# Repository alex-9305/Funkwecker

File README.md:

# Funkwecker
Hardware- und Softwareentwicklung eines Funkweckers

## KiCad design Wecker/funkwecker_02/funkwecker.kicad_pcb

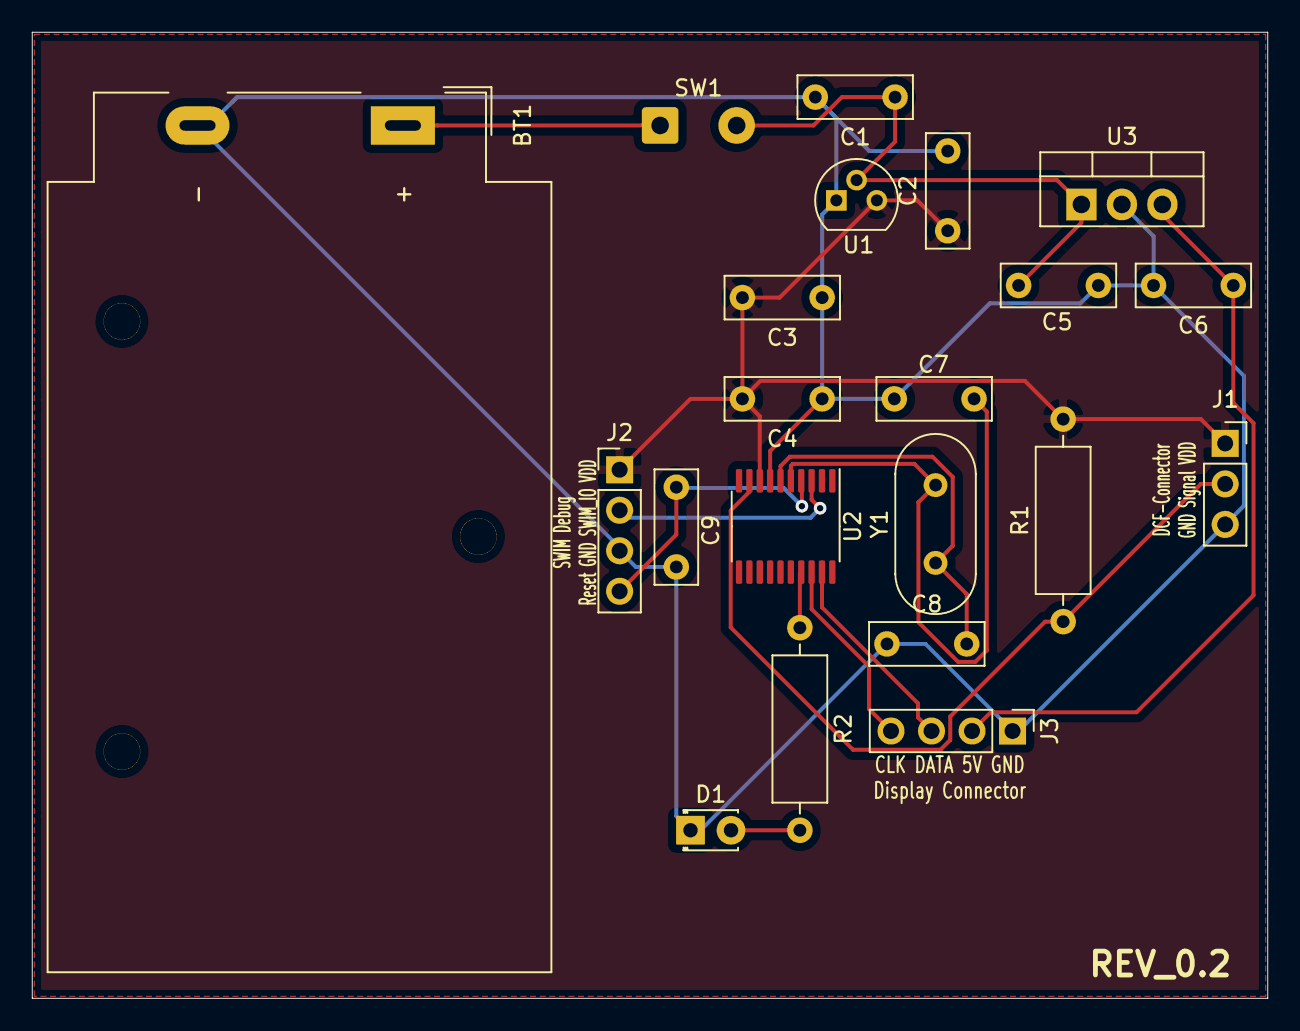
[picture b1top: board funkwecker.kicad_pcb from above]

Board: 2 copper layers, 77.5 x 60.6 mm, 21 parts (0 on the bottom side), 14 nets.

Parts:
BT1: 9VBlock; BatteryHolder_MPD_BA9VPC_1xPP3
C1, C2: 1µF; C_Disc_D7.0mm_W2.5mm_P5.00mm
C3, C9: 100nF; C_Disc_D7.0mm_W2.5mm_P5.00mm
C4: 10µF; C_Disc_D7.0mm_W2.5mm_P5.00mm
C5: 0.33µF; C_Disc_D7.0mm_W2.5mm_P5.00mm
C6: 0.1µF; C_Disc_D7.0mm_W2.5mm_P5.00mm
C7, C8: 20pF; C_Disc_D7.0mm_W2.5mm_P5.00mm
D1: Test_LED; LED_D1.8mm_W3.3mm_H2.4mm
J1: DCF77-Connector; PinSocket_1x03_P2.54mm_Vertical
J2: Debug-Interface; PinHeader_1x04_P2.54mm_Vertical
J3: LED-Display Connector (TM1637); PinHeader_1x04_P2.54mm_Vertical
R1: 100k; R_Axial_DIN0309_L9.0mm_D3.2mm_P12.70mm_Horizontal
R2: 1k; R_Axial_DIN0309_L9.0mm_D3.2mm_P12.70mm_Horizontal
SW1: Hauptschalter; SolderWire-0.5sqmm_1x02_P4.8mm_D0.9mm_OD2.3mm
U1: MCP1702-3302; TO-92
U2: STM8L051F3P; TSSOP-20_4.4x6.5mm_P0.65mm
U3: L7805; TO-220-3_Vertical
Y1: HC49U 16MHz; Crystal_HC49-U_Vertical

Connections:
+5V: C6.1, J3.2, U3.3
DCF_SIGNAL: J1.2, R1.1, U2.9
GND: BT1.2, C1.2, C2.2, C3.1, C4.1, C5.2, C6.2, C7.2, C8.1, C9.1, D1.1, J1.3, J2.3, J3.1, U1.1, U2.7, U3.2
LED_DISPLAY_CLK: J3.4, U2.18
LED_DISPLAY_DATA: J3.3, U2.19
unnamed: BT1.1, SW1.1
unnamed: D1.2, R2.2
OSC_IN: C7.1, U2.5, Y1.2
OSC_OUT: C8.2, U2.6, Y1.1
RESET: C9.2, J2.4, U2.4
SWIM_I_O: J2.2, U2.3
Test_LED: R2.1, U2.17
VCC: C1.1, C5.1, SW1.2, U1.2, U3.1
VDD: C2.1, C3.2, C4.2, J1.1, J2.1, R1.2, U1.3, U2.8

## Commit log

2021-12-19 Aktuellen Stand(rev.1) hochgeladen
2021-12-21 2.Revision angefangen
    NRST Kondensator hinzugefügt
2021-12-25 Rev 2: Fehler korrigiert und neue Anordnung
    Fehler:
    -Fehlender Kondensator am RESET-Pin
    -Fehlerhaftes Layout für beide Spannungsregler korrigiert
    -Benötigten Platz verringert
2022-08-20 Wechsel auf STM32F103 entwicklungsboard
2022-08-20 Projekt aufgesetzt und Anfang Programmierung
2022-08-26 Testcommit console Linux
2022-08-26 test2 unversioned file
2022-08-27 chosen config for controller
2022-10-19 Neustart Projekt mit STM32
2022-10-19 Konfigurationsdateien hinzugefügt
2022-10-19 Alte settings entfernt
2022-10-21 Hinzufügen der STM Peripheral Libraries
